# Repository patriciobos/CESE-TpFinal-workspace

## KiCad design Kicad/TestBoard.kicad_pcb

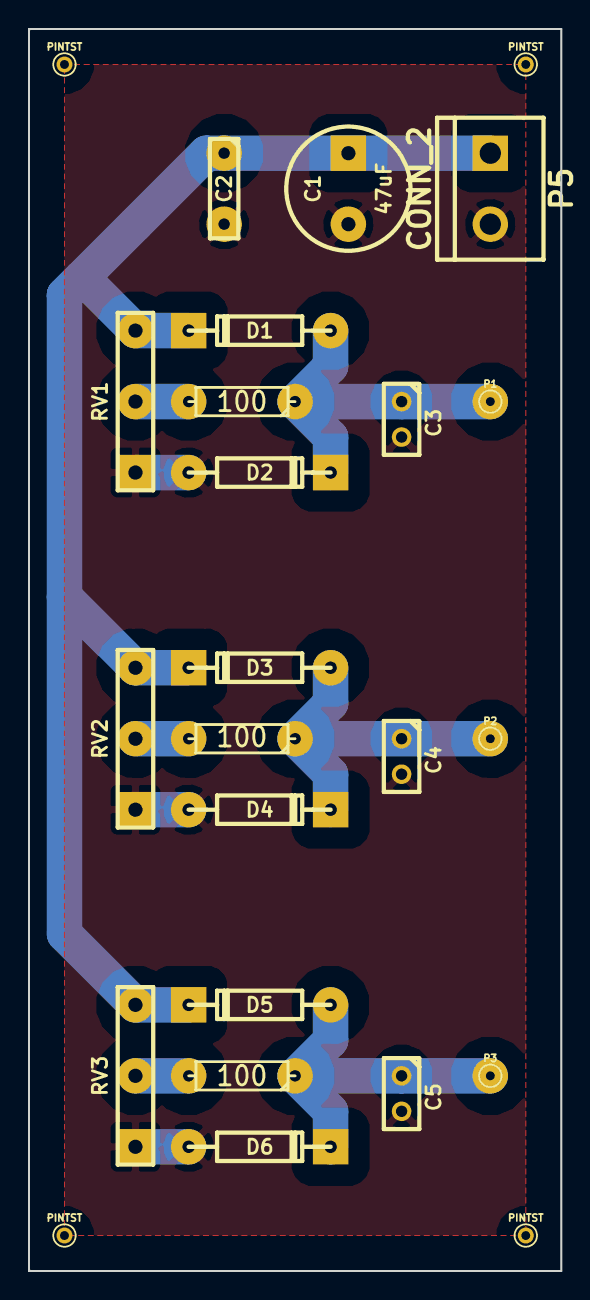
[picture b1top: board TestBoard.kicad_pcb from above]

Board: 2 copper layers, 38.1 x 88.9 mm, 25 parts (0 on the bottom side), 9 nets.

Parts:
C1: 47uF; C2V8
C2: 100nF; C2
C3, C4, C5: .1uF; C1
D1, D2, D3, D4, D5, D6: 1N4148; DO-41
P1, P2, P3: TST; PINTST
P5: CONN_2; bornier2
PINTST: Val*; PINTST
PINTST#2, PINTST#3, PINTST#4: Val*; PINTST
R1, R2, R3: 100; R3
RV1, RV2, RV3: 10K; Pote

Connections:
+12V: C1.1, C2.1, D1.2, D3.2, D5.2, P5.1, RV1.3, RV2.3, RV3.3
/ADC0: C3.1, D1.1, D2.2, P1.1, R1.1
/ADC1: C4.1, D3.1, D4.2, P2.1, R2.1
/ADC2: C5.1, D5.1, D6.2, P3.1, R3.1
GNDA: C1.2, C2.2, C3.2, C4.2, C5.2, D2.1, D4.1, D6.1, P5.2, RV1.1, RV2.1, RV3.1
unnamed: R3.2, RV3.2
unnamed: R1.2, RV1.2
unnamed: R2.2, RV2.2
unnamed: PINTST.1, PINTST#2.1, PINTST#3.1, PINTST#4.1

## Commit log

2016-05-26 initial commit webserver crash with malloc fail randomly
2016-06-09 transfiero ultimos cambios al repo auxiliar
2016-06-09 cambios en .gitignore
2016-06-09 elimino archivos generados en la compilacion
2016-06-09 finalmente la pegue con el .gitignore?
2016-06-09 habilito mallocFailHook como no bloqueante
2016-06-09 style.css para que entre bien la pagina en resolucion 1366x768
2016-06-09 agregue el .dll que necesita el makefsdata.exe y modifique el .gitignore para que no lo ignore
2016-06-09 agrego .dll para makefsdata.exe
2016-06-09 fsdata.c al repo
2016-06-10 modificaciones en la memoria con Sebastian en el LSE
2016-06-10 con la etiqueta "//task stack debug" marqué lugares del código donde achiqué los tamaños de stack de algunas tareas. anda mejor con eso. usé uxTaskGetStackHighWaterMark para ver el uso del stack.
2016-06-14 Trabajando sobre el control de las alarmas y ADC, están ambos inconcistentes
2016-06-15 Estado de el control de alarmas consistente. Se guarda el estado de los checkboxes durante la sesión del navegador.
    El control del ADC no resuelto
    problema de memoria no resuelto
2016-06-16 Estado de la memoria casi resulto. Malloc Fails si cago a palos la página.
2016-06-16 6 alarmas, 2 por sensor. JS ordenado y página actualizada.
2016-06-16 Se lee el valor de los sensores y los valores máximos de variables array. Modificaciones en la página web para usar todos índices de 0 a n
2016-06-21 cambios el feriado
2016-06-21 nuevos archivos de la pagina web
2016-06-21 acomodo los anchos de las columnas en la web corrijo los links de CGIs a control.shtml
2016-06-22 ADC funcionando
2016-06-23 Arreglado el menu de navegación en la web. Andan los adcs.
2016-06-23 Logica de control de las alarmas funciona. Falta resolver que cuando se deshabilita el control se apaguen los actuadores bajo control.
2016-06-24 Los botones se deshabilitan con JS si están siendo controlados. Cambia estilo .CSS para tener bordes redondeados en todos lados
2016-06-24 Agregado un tooltip a los botones deshabilitados por el control de alarmas
2016-06-24 Bajé MEM_SIZE a 1kb y el tiempo de refresco a 1seg. Se rompe al rato de uso.
2016-06-27 Agrego carpeta Resultados para analizar la performance del control Incrementé el stack de la task alarma para debugear los estados
2016-06-28 Ajuste de escala para la lectura de los ADCs. Cambios en la web para ver correctamente los valores. Nuevas series de datos para Ensayos a caja negra
2016-06-28 Cambios en los scripts MATLAB
2016-07-05 Retoque en la pagina web
2016-07-06 Agrego los .m de la carpeta Resultados
2016-07-07 Cambios trasnochados. cambie el div section: en lugar de position:fixed puse center y en lugar de margin left 0 puse 150 queda raro el scroll en la laptop
2016-07-07 retoque a framework.css
2016-07-07 cambios antes que corten la luz!
2016-07-07 retoques para emprolijar el código, algunos refactorings
2016-07-11 cambios para la version preliminar
2016-07-11 algo en actuators.c
2016-07-12 Fijo las posiciones en la página web
2016-07-12 cambios en la web. posiciones fijas
2016-07-13 modificaciones en el CSS de framework
2016-07-13 Agrego barras de gráficos para los sensores
2016-07-15 cambios de color en la web
2016-07-18 cambios en la interfaz. color en las barras. cambios en la asignación de memorio
2016-07-22 Control de actuadores asociado a las salidas digitales de la CIAA
2016-07-22 Ajustes de memoria
2016-07-25 KICAD
2016-07-26 Ajustes en la página para resolucion 1280x720
2016-07-26 más ajustes en la resolución de la pagina web
2016-07-26 ancho de header y footer al 100% para pantallas con más resolución
2016-07-26 retoques en los anchos de header y footer
2016-08-01 PCB con potenciometros
2016-08-01 ajuste para resolución de 1024
2017-09-25 actualizo después de muuucho tiempo archivos no incluidos
